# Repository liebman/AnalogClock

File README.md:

# AnalogClock 2.X

Project to sync analog clocks to a few milliseconds using NTP for time synchronization. Details of operation can be found in this [blog post](https://blog.taboola.com/analog-clocks-ntp/)

[I2CAnalogClock](I2CAnalogClock) contains the code for the ATTiny85 as an I2C based Analog Clock controller.  I am now using [PlatformIO](https://platformio.org/) for development.

[SynchroClock](SynchroClock) contains the code for the ESP8266 module.   I am now using [PlatformIO](https://platformio.org/) for development.

[NTPTest](NTPTest) contains a framework for testing the NTP class in an accelerated manor on linux or MacOS saving days of waiting for results.

[eagle](eagle) contains the [Eagle](https://www.autodesk.com/products/eagle/overview) design files and the BOM.

## Features

* Automatic daylight saving time adjustments
* Clock position & configuration saved on power fail
* Low power consumption: approx. 0.25ma in early testing
* adjustable tick/adjust pulse width/duty cycle/delay should support most one second "tick" (non-sweep) clocks.
* NTP implementation computes drift and uses that to increase accuricy between NTP updates

## Configuration

   When the clock is initially powered on it creates a wifi captive portal.  It will show up in the list of available wifi networks as SynchroClockXXXXXXX (where the X’s are some number).  Configuration mode can be forced by holding down the reset button until the LED is turns on and stays on for at least 2 seconds then releasing it. NOTE that if you conrinue holding the reset button for more than 10 seconds the LED will go back off initiating a factory reset to default settings. When you connect to this you are given a menu that lets you set many configuration options:

* Wifi Network (SSID)
* Wifi Network password
* Clock Position - enter the current time shown on the clock as HH:MM:SS.
* NTP Server to sync with
* 1st time change as 6 fields (US/Pacific would be: 2 0 0 3 2 -25200 meaning the second Sunday in March at 2am we change to UTC-7 hours, and Israel: -1 0 -2 3 2 10800 meaning the Friday before the last Sunday of in March at 2am we change to UTC+3)
  * occurrence - 2 would be the second occurrence of the day of week specified, -1 would be the last one.
  * day of week - where 0 = Sunday
  * days offset - +|- days, used for "the Friday before the last Sunday"
  * month - where 1 = January
  * hour - where 0 = midnight
  * time offset - this is the offset in seconds from UTC
* 2nd time change as 5 fields as described above (US/Pacific: 1 0 0 11 2 -28800 meaning the first Sunday in November at 2am we change to UTC-8 hours, and Israel: -1 0 0 10 2 7200 meaning the last Sunday of October we change to UTC-2)

Advanced options:

* Stay Awake - when set true the ESP8266 will not use deep sleep and will run a small web servers allowing various operations to be performed with an http interface.
* Tick Pulse - this is the duration in milliseconds of the “tick”.
* Tick Duty Cycle - the percentage of time that the tick is on using PWM
* Adjust Start Pulse - this uis the duration in milliseconds of the initial pulse of an adjustment
* Adjust Pulse - this is the duration in milliseconds of the “tick” used to advance the clock rapidly.
* Adjust Duty Cycle - the percentage of time that the tick is on using PWM
* Adjust Delay - this is the delay in milliseconds between “ticks” when advancing the clock rapidly.
* Network Logger Host - (optional) hostname to send log lines to.
* Network Logger Port - (optional) tcp port to send log lines to.
* Clear NTP Persist - when set 'true' clears any saved adjustments and drift calculations.

## Schematic

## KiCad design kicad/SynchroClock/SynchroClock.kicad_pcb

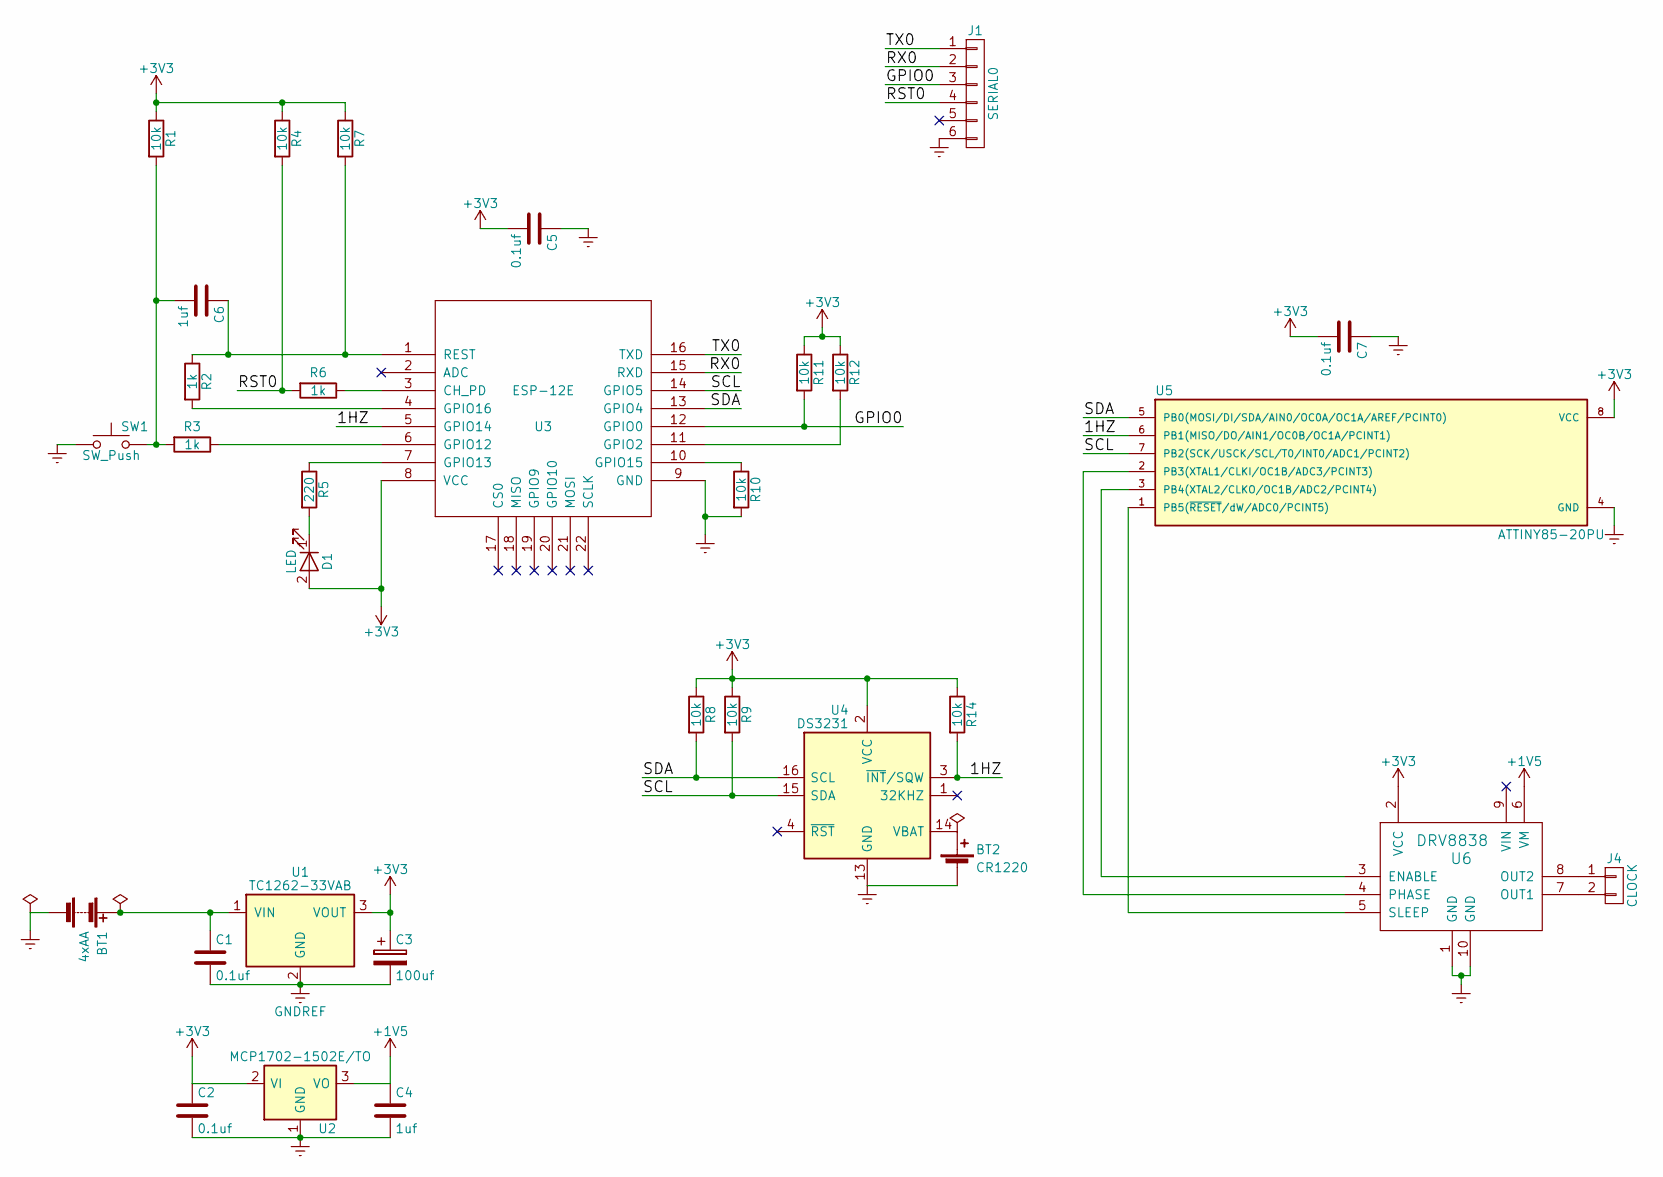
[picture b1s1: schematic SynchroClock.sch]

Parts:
BT1: 4xAA; JST_XH_B02B-XH-A_02x2.50mm_Straight
BT2: CR1220; CR1220-smd
C1, C2, C5, C7: 0.1uf; C_Disc_D5.0mm_W2.5mm_P2.50mm
C3: 100uf; CP_Radial_D6.3mm_P2.50mm
C4, C6: 1uf; C_Disc_D5.0mm_W2.5mm_P2.50mm
D1: LED; LED_D3.0mm
J1: SERIAL0; Socket_Strip_Straight_1x06_Pitch2.54mm
J4: CLOCK; Pin_Header_Straight_1x02_Pitch2.54mm
R1, R4, R7, R8, R9, R10, R11, R12, R14: 10k; R_Axial_DIN0207_L6.3mm_D2.5mm_P2.54mm_Vertical
R2, R3, R6: 1k; R_Axial_DIN0207_L6.3mm_D2.5mm_P2.54mm_Vertical
R5: 220; R_Axial_DIN0207_L6.3mm_D2.5mm_P2.54mm_Vertical
SW1: SW_Push; SW_PUSH_6mm
U1: TC1262-33VAB; TO-220_Vertical
U2: MCP1702-1502E/TO; TO-92_Inline_Narrow_Oval
U3: ESP-12E
U4: DS3231; SOIC-16W_7.5x10.3mm_Pitch1.27mm
U5: ATTINY85-20PU; DIP-8_W7.62mm
U6: DRV8838; DIP-10_W7.62mm

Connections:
+1V5: C4.1, U2.3 (VO), U6.6 (VM)
+3V3: C2.1, C3.1, C5.2, C7.2, D1.2 (A), R1.1, R4.1, R7.1, R8.1, R9.1, R11.1, R12.1, R14.1, U1.3 (VOUT), U2.2 (VI), U3.8 (VCC), U4.2 (VCC), U5.8 (VCC), U6.2 (VCC)
/1HZ: R14.2, U3.5 (GPIO14), U4.3 (~INT~/SQW), U5.6 (PB1(MISO/DO/AIN1/OC0B/OC1A/PCINT1))
/GPIO0: J1.3, R11.2, U3.12 (GPIO0)
/RST0: J1.4, R4.2, R6.2
/RX0: J1.2, U3.15 (RXD)
/SCL: R9.2, U3.14 (GPIO5), U4.15 (SDA), U5.7 (PB2(SCK/USCK/SCL/T0/INT0/ADC1/PCINT2))
/SDA: R8.2, U3.13 (GPIO4), U4.16 (SCL), U5.5 (PB0(MOSI/DI/SDA/AIN0/OC0A/OC1A/AREF/PCI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)
/TX0: J1.1, U3.16 (TXD)
GNDREF: BT1.2 (-), BT2.2 (-), C1.2, C2.2, C3.2, C4.2, C5.1, C7.1, J1.6, R10.2, SW1.1, U1.2 (GND), U2.1 (GND), U3.9 (GND), U4.5 (NC), U4.6 (NC), U4.7 (NC), U4.8 (NC), U4.9 (NC), U4.10 (NC), U4.11 (NC), U4.12 (NC), U4.13 (GND), U5.4 (GND), U6.1 (GND), U6.10 (GND)
unnamed: BT1.1 (+), C1.1, U1.1 (VIN)
unnamed: BT2.1 (+), U4.14 (VBAT)
unnamed: C6.1, R2.1, R7.2, U3.1 (REST)
unnamed: C6.2, R1.2, R3.2, SW1.2
unnamed: D1.1 (K), R5.2
unnamed: J4.1, U6.8 (OUT2)
unnamed: J4.2, U6.7 (OUT1)
unnamed: R2.2, U3.4 (GPIO16)
unnamed: R3.1, U3.6 (GPIO12)
unnamed: R5.1, U3.7 (GPIO13)
unnamed: R6.1, U3.3 (CH_PD)
unnamed: R10.1, U3.10 (GPIO15)
unnamed: R12.2, U3.11 (GPIO2)
unnamed: U5.1 (PB5(~RESET~/dW/ADC0/PCINT5)), U6.5 (SLEEP)
unnamed: U5.2 (PB3(XTAL1/CLKI/OC1B/ADC3/PCINT3)), U6.4 (PHASE)
unnamed: U5.3 (PB4(XTAL2/CLKO/OC1B/ADC2/PCINT4)), U6.3 (ENABLE)

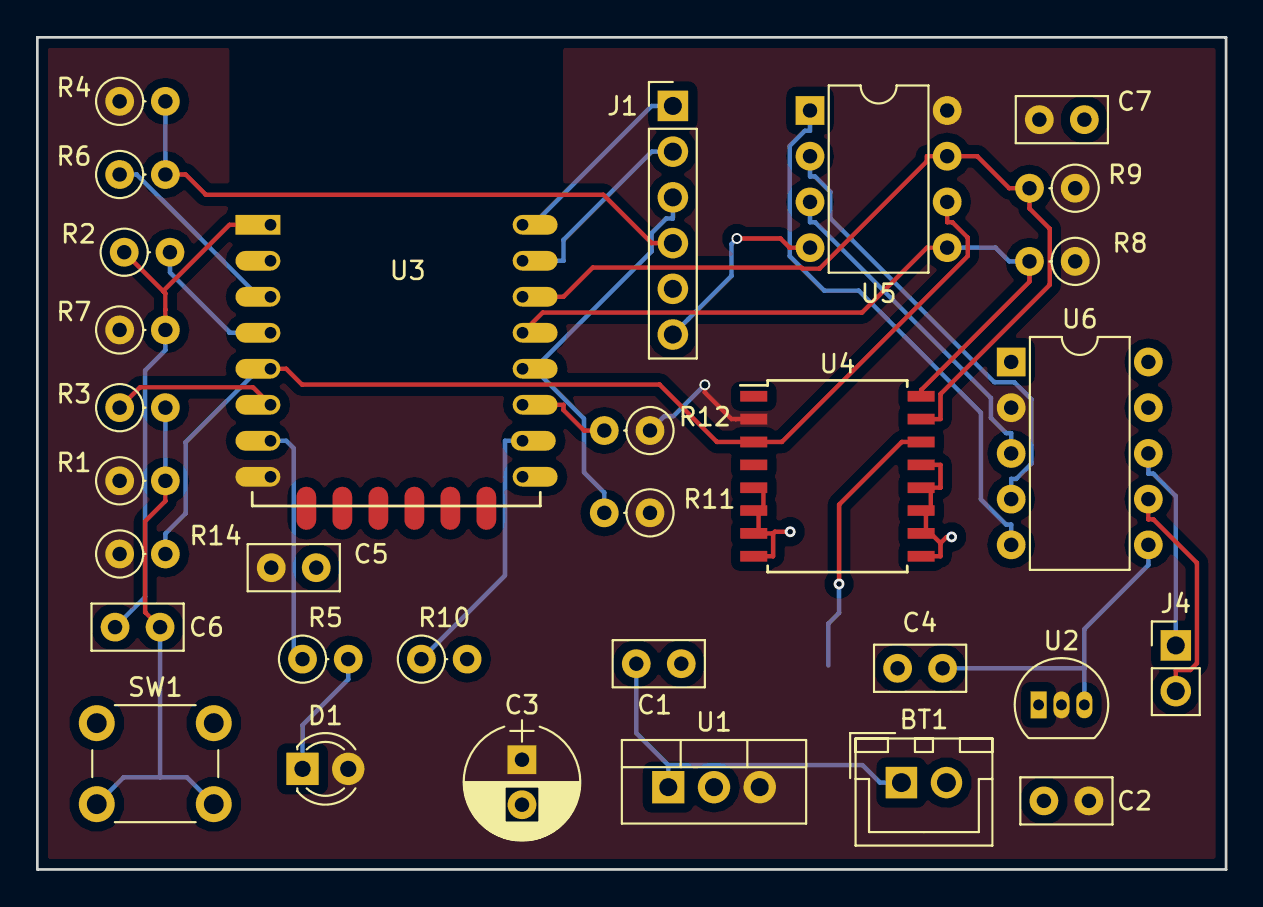
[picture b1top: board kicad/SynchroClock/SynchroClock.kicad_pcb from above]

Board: 2 copper layers, 66.0 x 46.2 mm, 32 parts (1 on the bottom side), 26 nets.

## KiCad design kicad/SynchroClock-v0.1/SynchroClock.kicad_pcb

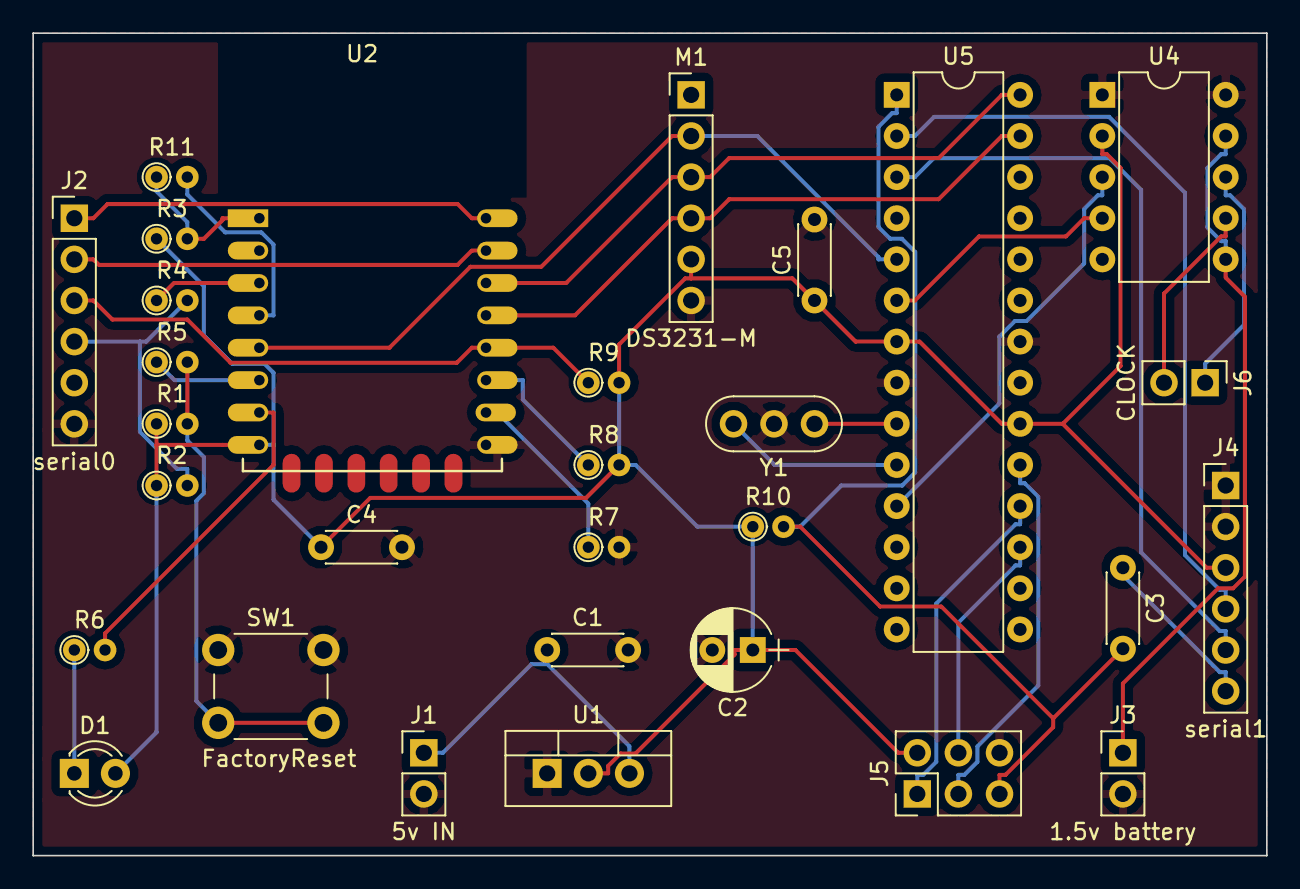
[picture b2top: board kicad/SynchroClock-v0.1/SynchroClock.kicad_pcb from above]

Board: 2 copper layers, 76.2 x 50.8 mm, 30 parts (0 on the bottom side), 33 nets.

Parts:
C1: 100nf; C_Disc_D4.3mm_W1.9mm_P5.00mm
C2: 100uf; CP_Radial_D5.0mm_P2.50mm
C3, C4, C5: 0.1uf; C_Disc_D4.3mm_W1.9mm_P5.00mm
D1: LED; LED_D3.0mm
J1: 5v IN; Pin_Header_Straight_1x02_Pitch2.54mm
J2: serial0; Pin_Header_Straight_1x06_Pitch2.54mm
J3: 1.5v battery; Pin_Header_Straight_1x02_Pitch2.54mm
J4: serial1; Pin_Header_Straight_1x06_Pitch2.54mm
J5: ICSP; Pin_Header_Straight_2x03_Pitch2.54mm
J6: CLOCK; Pin_Header_Straight_1x02_Pitch2.54mm
M1: DS3231-M; Pin_Header_Straight_1x06_Pitch2.54mm
R1, R2, R3, R7, R8, R9, R10: 10k; R_Axial_DIN0204_L3.6mm_D1.6mm_P1.90mm_Vertical
R4, R5, R11: 1k; R_Axial_DIN0204_L3.6mm_D1.6mm_P1.90mm_Vertical
R6: 220; R_Axial_DIN0204_L3.6mm_D1.6mm_P1.90mm_Vertical
SW1: FactoryReset; SW_PUSH_6mm
U1: LM1117-3.3; TO-220_Vertical
U2: ESP-12E
U4: DRV8838; DIP-10_W7.62mm
U5: ATMEGA328-PU; DIP-28_W7.62mm
Y1: 8Mhz; Resonator_muRata_CSTLSxxxG-3pin_w8.0mm_h3.0mm

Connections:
+1.5: J3.1, U4.6, U4.9
+3.3: C2.1, C4.1, C5.1, D1.2, J4.3, J5.2, M1.5, R1.1, R2.1, R3.1, R8.2, R9.2, R10.1, U1.2, U2.8, U4.2, U5.7, U5.20
/1HZ: M1.2, U2.5, U5.5
/GPIO0: J2.3, R9.1, U2.12
/MISO: J5.1, U5.18
/MOSI: J5.4, U5.17
/RST0: J2.4, R2.2, R4.2
/RST1: C3.2, J5.5, R10.2, U5.1
/RX0: J2.2, U2.15
/RX1: J4.4, U5.2
/SCK: J5.3, U5.19
/SCL: M1.3, U2.14, U5.28
/SDA: M1.4, U2.13, U5.27
/TX0: J2.1, U2.16
/TX1: J4.5, U5.3
GND: C1.2, C2.2, C4.2, C5.2, J1.2, J2.6, J3.2, J4.1, J4.2, J5.6, M1.6, R7.2, SW1.1, U1.1, U2.9, U4.1, U4.10, U5.8, U5.22, Y1.2
unnamed: C1.1, J1.1, U1.3
unnamed: C3.1, J4.6
unnamed: D1.1, R6.1
unnamed: J6.1, U4.8
unnamed: J6.2, U4.7
unnamed: R1.2, R5.2, SW1.2
unnamed: R4.1, U2.3
unnamed: R5.1, U2.6
unnamed: R6.2, U2.7
unnamed: R7.1, U2.10
unnamed: R8.1, U2.11
unnamed: R3.2, R11.1, U2.1
unnamed: R11.2, U2.4
unnamed: U4.3, U5.11
unnamed: U4.4, U5.6
unnamed: U5.9, Y1.1
unnamed: U5.10, Y1.3

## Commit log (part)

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2017-03-23 Added start of schematic (its going to change a lot!)
2017-03-23 using atmega328 for now
2017-03-23 added eclipse project settings
2017-03-25 added conditionals for ATtiny85
2017-03-25 more tuning, added in/out of position as HH:MM:SS
2017-03-25 use interrupt timers for ticks conditional on #define USE_TIMER
2017-03-25 always use timer/interrupts, remove USE_TIMER conditionals
2017-03-25 reduce delay/duration sizes to 8bit unsigned
2017-03-26 disable serial debug messages
2017-03-26 allow specifing noon/midnight as 12:00:00 instead of 00:00:00
2017-03-26 update schematic (WIP)
2017-03-26 refactor - move clock interface to seperate class
2017-03-26 added diodes to drop clock output voltage
2017-03-26 fixed origin timestamp, attempted to compute delay and offset (not working)
2017-03-26 more schematic work
2017-03-29 use 1.5v to drive clock - better timing 16ms tick pusles and an adjust delay of 8ms
2017-03-30 fix overflows
2017-03-31 compute NTP offset correctly
2017-03-31 use offset to set time, create dbug print macros instead of Serial.print*
2017-03-31 cleanup, make messages optional
2017-04-19 Fleshout circuit more
2017-04-20 v1 PCB layout
2017-04-23 lock in v0.1 kicad
2017-04-25 add interrupt/timer config for ATTiny85
2017-04-29 ATTiny85 - working sort of.... i2c hangs on first request after a write
2017-04-30 Cleanup - no longer need wire library wrapper since USIWire is compatable!
2017-04-30 Use sleep to reduce power
2017-05-02 improved NTP
2017-05-07 update default adjust delay to 12ms, up from 8ms
2017-05-07 added factory restart support and saving config values in EEPROM
2017-05-08 decrement right after check - not after delays!
2017-05-08 added config saved to EEPROM (only timezone offset for now)
2017-05-11 added more config options (limit to 10 without hacking the WifiManager lib!)
2017-05-11 added old version new version updated a bit - still not done or compleatly tested
2017-05-12 remove eclipse project settings
2017-05-13 Fixed race conditions with position and adjustment value during adjustment
2017-05-13 added sleep_delay to sleep DRV8838 to save power.
2017-05-14 added config for DRV sleep delay
2017-05-14 use timer (not loop) for adjustment, now both tick and adjust are interrupt/timer driven always fire one tick on startup to sync clock motor
2017-05-14 format cleanup
2017-05-14 use idle sleep for now (working on power down sleep)
2017-05-15 now power down the DRV8838 and the I2CAnalogClock MCU to save power (from 2.6ma+ to 0.74ma avg!!!) Converted the ATTiny85 reset pin to an output as I needed a pin for teh DRV disable!
2017-05-15 updated with reset & sleep changes
2017-05-26 new implementation to talk with DS3231 w/wire error checking added some wire error checking to Clock I2C bus Recovery method added via WireUtils
2017-05-26 added error codes for netRTCfromNTP()
2017-05-27 stability improvements and cleanup
2017-05-31 added mode debug states
2017-05-31 cleanup warning
2017-05-31 added Logger to hadle both Serial & network logging
2017-06-01 clean up unused code detect bad DateTime objects if readtime succedded but gave bad data
2017-06-01 declare vsnprintf as its not covered in any includes :-(
2017-06-04 If we wake with the reset button pressed and sleep_delay_left then the radio is off, use a deepSleep to turn it back on.
2017-06-04 added comment about short deep sleep
2017-06-04 use updated WiFiManager to allow more params
2017-06-04 adjust defaults, cleanup field sizes
2017-06-06 make sure newline is sent to TCP!
2017-06-07 created ConfigParam to clean up wifi config param code moved TZUtils into new TimeUtils that has many time related static methods
2017-06-07 handle negitive values for weel specification to indicate last, second to last etc
2017-06-07 added config params for 2 time changes to adn from DST
2017-06-15 compute a long double version of offset so we can easialy check abs value for when to set RTC
2017-06-17 use median of last values if ntp offset comes back as >900ms
2017-06-17 stop the clock for up to 60 seconds to handle negative delta when setting from RTC
2017-06-20 use 64bit ints for offset cleanup median code
2017-06-27 Apply license
2017-06-27 switch to eagle cad for hardware
2017-06-28 fixed the network logger port configuration
2017-07-03 Add a TCP connect timeout and max connect attemps till we bail on TCP and stick with serial only.
2017-07-03 Last commit before removal
2017-07-03 Use new NTP Class
2017-07-04 Persist servername and ip address, use persisted ip address if server name remains unchanged. TBD lookup server address again if reachability is bad.
2017-07-04 improve NTP accuracy
2017-07-06 Switch offset to double, jitter calculations for observation.
2017-07-14 consolidate Logger #defines
2017-07-14 major refactor of NTP code, now includes NTPTest framework to allow NTP debugging on MacOS/unix
2017-07-15 added a debug hack to hard code the WiFi info added some formatting
2017-07-19 correct the mdelay calculation for negative offsets
2017-07-19 disable DS3231 debug
2017-07-19 switch to 1.5v for clock voltage regulator
2017-07-23 updated NTP calculations
2017-07-25 improved poll interval calculation based on our trust of the drift value
2017-07-25 minor comment update
2017-07-25 Updated NTP algo with drift. Still need to find a way to speed up initial sync and drift calculation.
2017-07-26 updated algo
2017-07-28 Improvements on ntp poll interval - still work in progress
2017-07-28 more poll interval testing/improvements
2017-07-29 tune threshold from 40ms to 20ms to compute drift faster
2017-07-30 added schematic image
2017-09-01 Code now works with basic h bridge, now need to update the schematic/board
2017-09-09 no longer have to use stay awake logic, timeing still not right for AP duration/delay/duty
2017-09-09 "development" version - board that does not have the clock driver
2017-09-12 correctly apply current clock settings if its running over the config, if its not running then the config wins
2017-09-12 removed un-needed non-PWM & DRV code
2017-09-12 cleanup to remove un-needed sleep delay as it was only used for the DRV motor controler
2017-09-13 minor cleanup / set current defaults in I2CAnalogClock
2017-09-16 Updated for v2
    Now uses PWM for ticks (saves power)
    No longer using motor controller (also saves power)
2017-09-16 add version
2017-09-16 updated schematic for current Alpha version
2017-09-17 no real changes
2017-09-17 basic powerfail now works - still need to add more data to be saved
2017-09-17 added power fail circuit for ATtiny85 added BOM save all clock properties at power fail
2017-09-18 updated schematic
2017-09-21 document attiny8 fuse settings set register with PWM_TOP so it can be changed
2017-09-24 added powerfail detection and saving of clock position and state (tick or tock & enababled or not) I2CAnalogClock (ATtiny) now has its config saved
2017-10-02 remove 4mhz option + small cleanups
2017-10-02 cleanup clock save config command added default log address/port (need to disable before production ready) remove clock timeing settings from config as they are saved on the ATtiny85 added defined de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
2017-10-07 board version 2.1
2017-10-07 board 2.1a
2017-10-08 updated schematic for readme
2017-10-21 cleaup readme a bit
2017-10-22 Apply potential timezone changes after adjusting RTC.
2017-10-23 Sometimes the RTC is not readable, retry when that happens during set rtc from offset
2017-10-26 Fixes #7
2017-10-26 initial refactor - debug enabled #6
2017-10-26 Implememnted "days offset" (#6)
2017-10-26 use updated version of my WiFiManager changes to allow more than 10 params.
2017-10-26 disable WiFiManager debug messages
2018-03-21 added timezone info use actual pin numbers so we can use generic board
2018-03-22 try running travis
2018-03-22 fixes
2018-03-22 try travis
2018-03-22 fix "case" typo Dlog.h -> DLog.h
2018-03-22 add PinChangeInterrupt lib
2018-03-22 added travis build image
2018-03-22 dynamically allocate wifi params
2018-03-24 A bit of cleanup
2018-03-24 enable clock on OTA success if it was enabled before OTA started
2018-03-25 Implement factory reset - resolves #10 Disable config ports in autoConnect - resolves #11
    Requires: https://github.com/tzapu/WiFiManager/pull/575
2018-03-25 need branch pf WiFiManager to build for now
2018-03-25 SynchroClock works with platformio
2018-03-27 factory reset was very broken. Now working!
2018-03-28 use getEdgeSyncedTime to get time synched to second start (with retries)
2018-03-28 use development version of WiFiManager
2018-03-28 include time.h headers
2018-03-28 added logging connection timeout/max attempts improve logging of chip id and versions
2018-04-03 attempt with platformio
2018-04-03 try sudo
2018-04-03 no update
2018-04-03 testing travis config
2018-04-03 Build with platformio (#12)
    Include platformio builds as part of CI. This is a first step to adding release generation from travis builds.
2018-04-05 use a modified fork of the arduino platformio framework to get updated ATTiny support
2018-04-05 change log prefix to seconds since boot + chip ID
2018-04-06 added submodules so we controle the versions
2018-04-06 build attempt using submodules
2018-04-06 fix hardware folder for arduino build on travis
2018-04-06 move esp8266 hardware to be more arduino like
2018-04-06 correct platform spec for esp
2018-04-06 remove last vestages of platformio
2018-04-06 Drop platformio and use submodules to load hardware and libraries from git (#13)
    * added submodules so we controle the versions
    * remove platformio
2018-04-20 hold button for 1 second for config mode, 10 more seconds for factory reset
2018-04-28 Backlink to CADLAB.io has been added.
2018-06-17 added syslg & cleanup SSID/Device name
2018-07-22 update to most recient working WifiManager
2018-08-12 updated WiFiManager & core
2018-08-18 updated WiFiManager
2018-08-18 update WiFiManager again
2018-08-18 update esp8266 core
2018-12-21 fix submodule
2018-12-21 adjust esp8266 device settings for updated core
2018-12-21 adjust esp8266 device settings for updated core some more
2019-07-16 switch to platformIO
2019-07-16 fix travis
2019-07-16 update readme for platformio & reset changes
2019-07-24 add platformio fuse setting and correct cpu freq for attiny85
2019-07-28 add workaround to prevent flash erase when using the platformio fuses target
2019-08-25 set default timechange settings from platformio.ini via build_flags
2019-08-25 fix issues with python3
2019-08-25 Support a local.init to add private extensions to platformio.init
2019-08-25 sync clock with RTC when WiFi connect fails in case of power outage where WiFi is not available
2019-08-25 Add include and test directories for future use and because platformio init creates them even with an existing project.
2019-08-30 started unit tests (its a work in progress) moved many file to include & lib for easy access from unit tests broke pin definitions out into a seperate include file for easy access from tests
2019-09-06 - increase CLOCK_STRETCH_LIMIT - bump SynchroClock version to 1.1.6 - define NTP_REQUEST_COUNT in platformio.ini for >1 NTP req's per cycle when more than one NTP choose the lowest delay - fix warnin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
2019-09-08 set drift_timestamp usint EPOCH not NTP timestamp
2019-09-08 fix poll interval calculation in getPollInterval() update version to 1.1.8
2019-09-09 improve selection of samples for drift estimate by using same criteria as for selecting offisets to use. version 1.1.9
2019-09-14 include pio env name in version string timestamps in samples now reflects new time and not time before offset adjustment don't include the initial first sample offset in estimated drift calculation S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
2019-09-18 bump version to 1.1.11 print current time (GMT) with timestamps 10 samples first sample set in 4 hours
2019-09-23 added a few comments and small debug fix
2019-09-25 only compute drift if we have at least 4 valid intervals bump version to 1.1.12
2021-09-08 Update to Espressif8266 2.6.3 toolchain
    This necessitates the removal (temporarily, at least) of -Werror so we
    can complete a compilation successfully.
2021-09-08 Use GitHub Actions
    Since my balance went negative on Travis-CI, it has never built anything for me.
    Switch to GitHub Actions which works arguably better than Travis.
2021-09-08 GitHub Actions: remove staging env
    The staging environment does not work, so remove it from CI for now.
2021-09-08 Update the repo to more modern toolchain (#21)
    * Update to Espressif8266 2.6.3 toolchain
    This necessitates the removal (temporarily, at least) of -Werror so we
    can complete a compilation successfully.
    * Update mkdata.py for Python 3
    Python 2.7 has been sunsetted since January 1, 2020. Update the builder
    to use Python 3.9 as it is the latest stable version.
